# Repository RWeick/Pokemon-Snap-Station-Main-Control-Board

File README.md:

# Pokemon-Snap-Station-Main-Control-Board
The schematic and gerbers for an N64 Pokemon Snap Station Main Control Board

PCB Thickness: 1.6 mm

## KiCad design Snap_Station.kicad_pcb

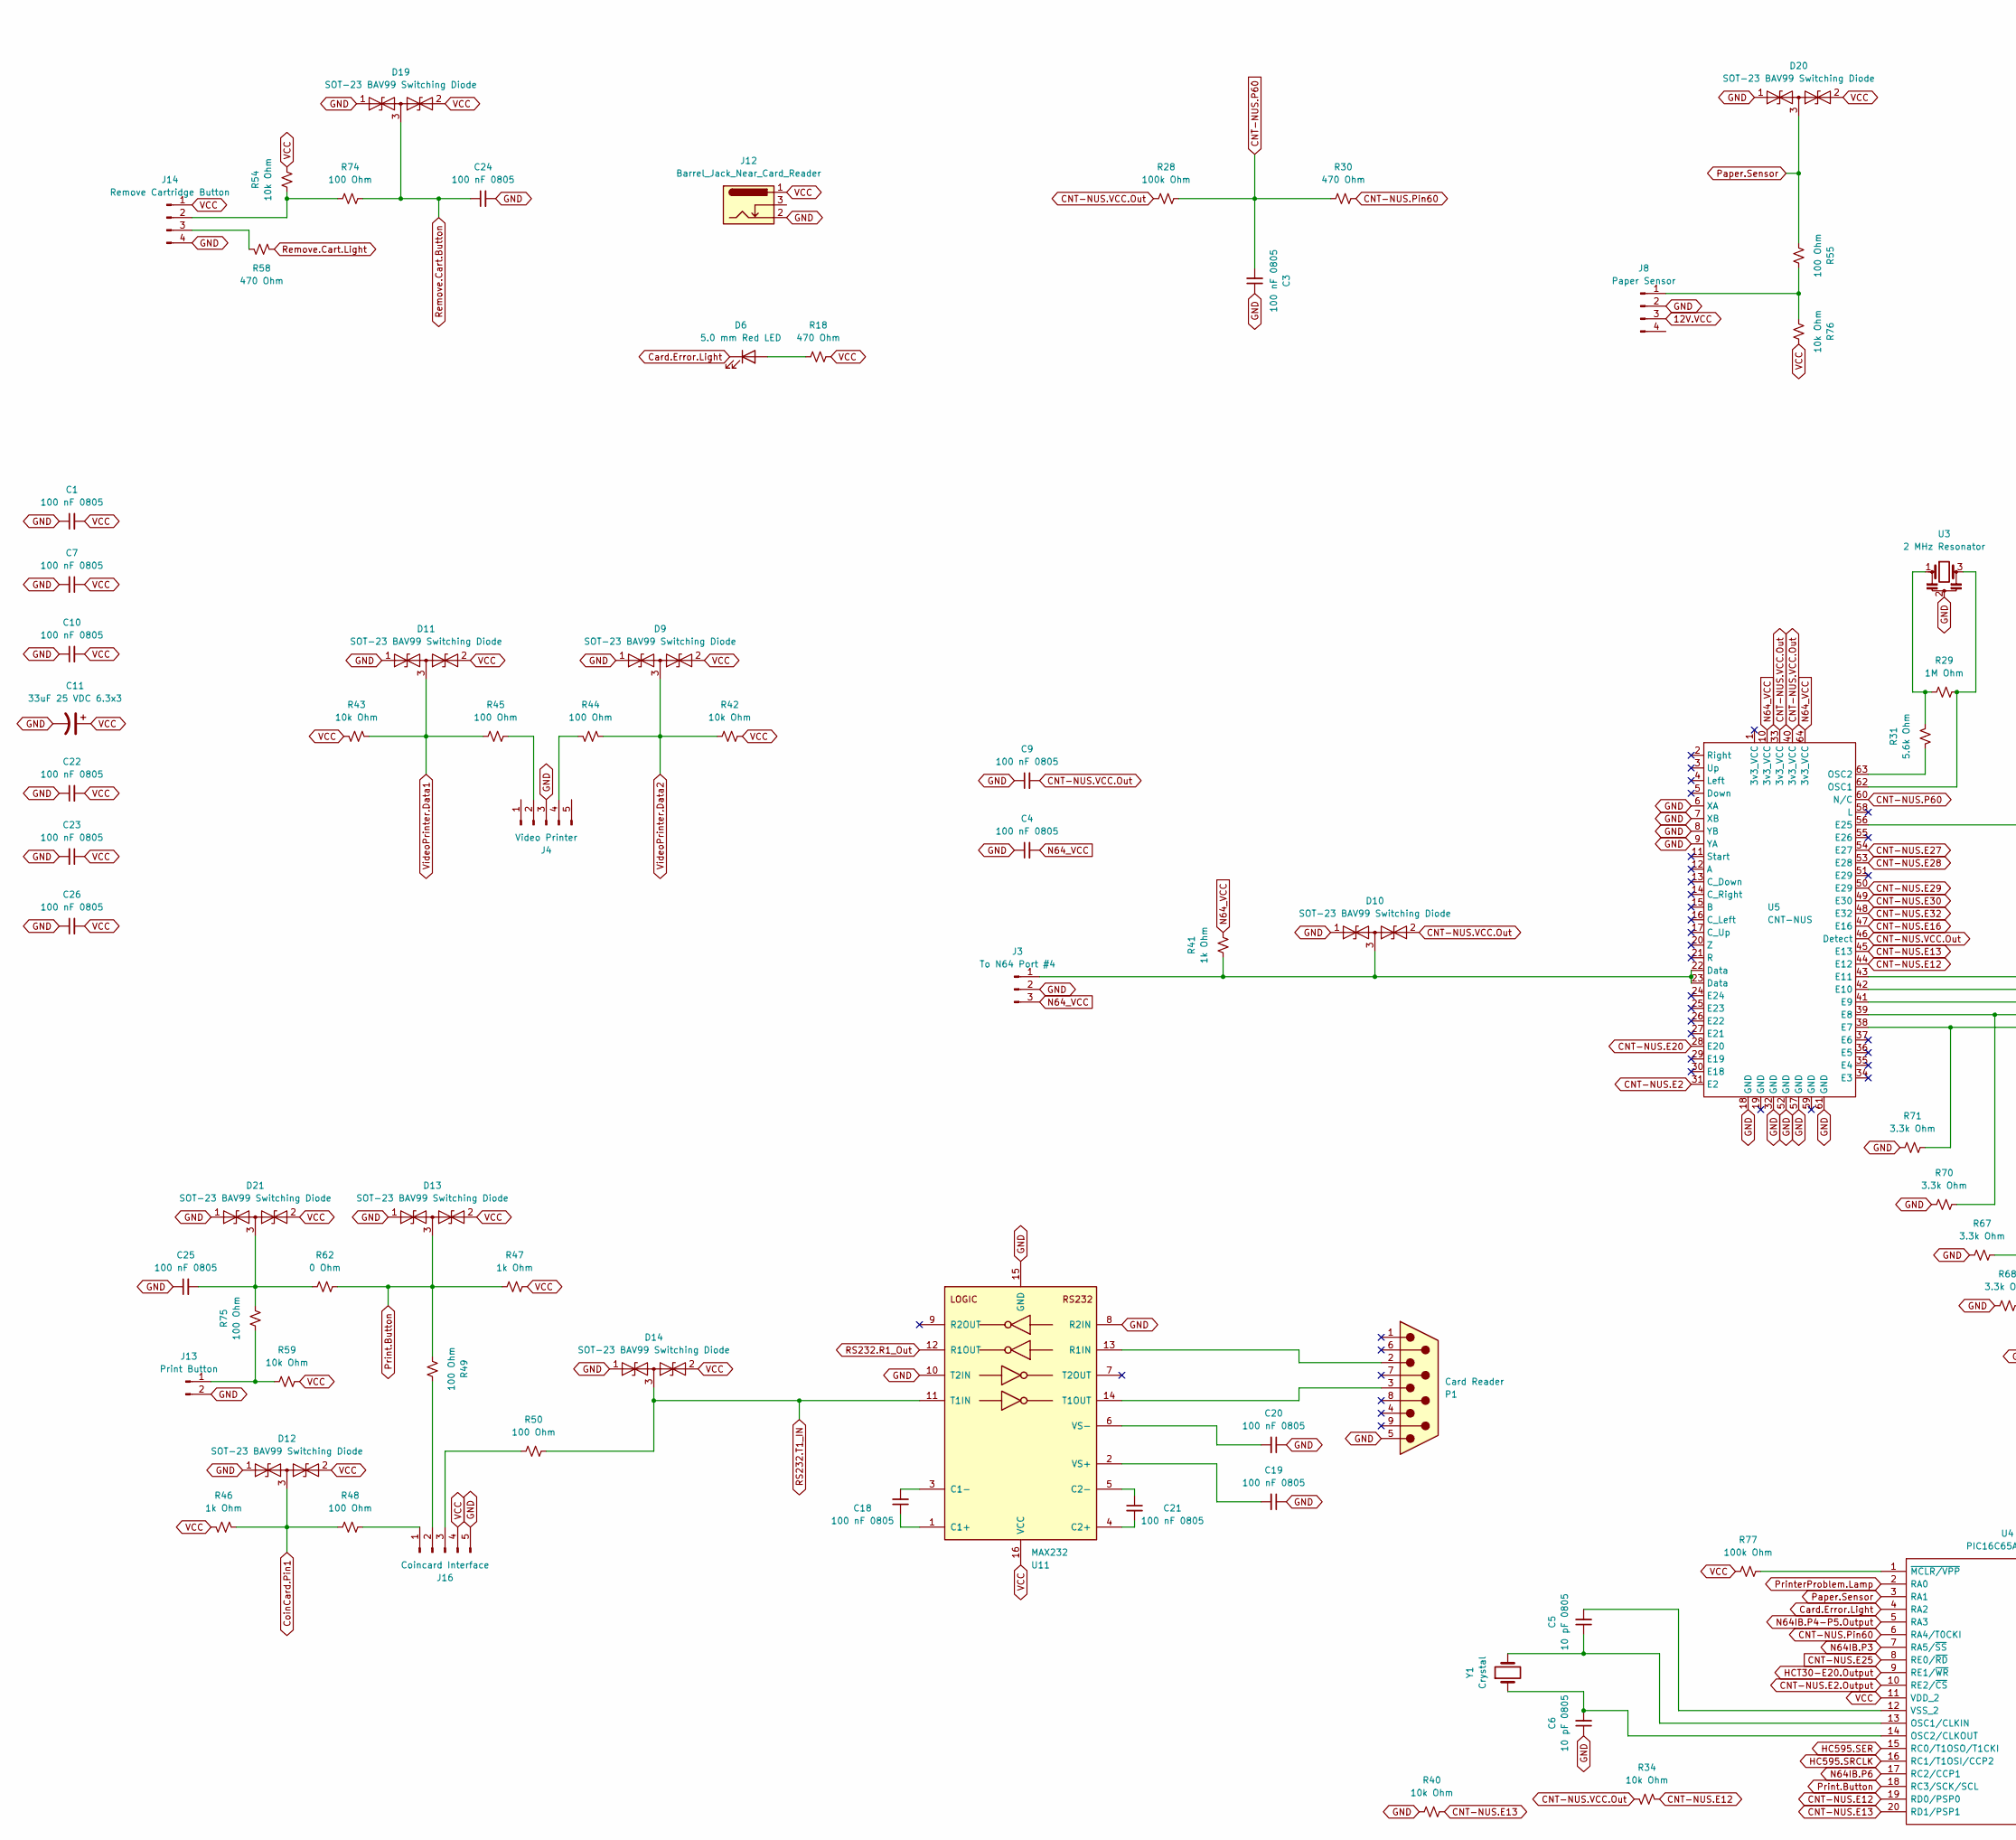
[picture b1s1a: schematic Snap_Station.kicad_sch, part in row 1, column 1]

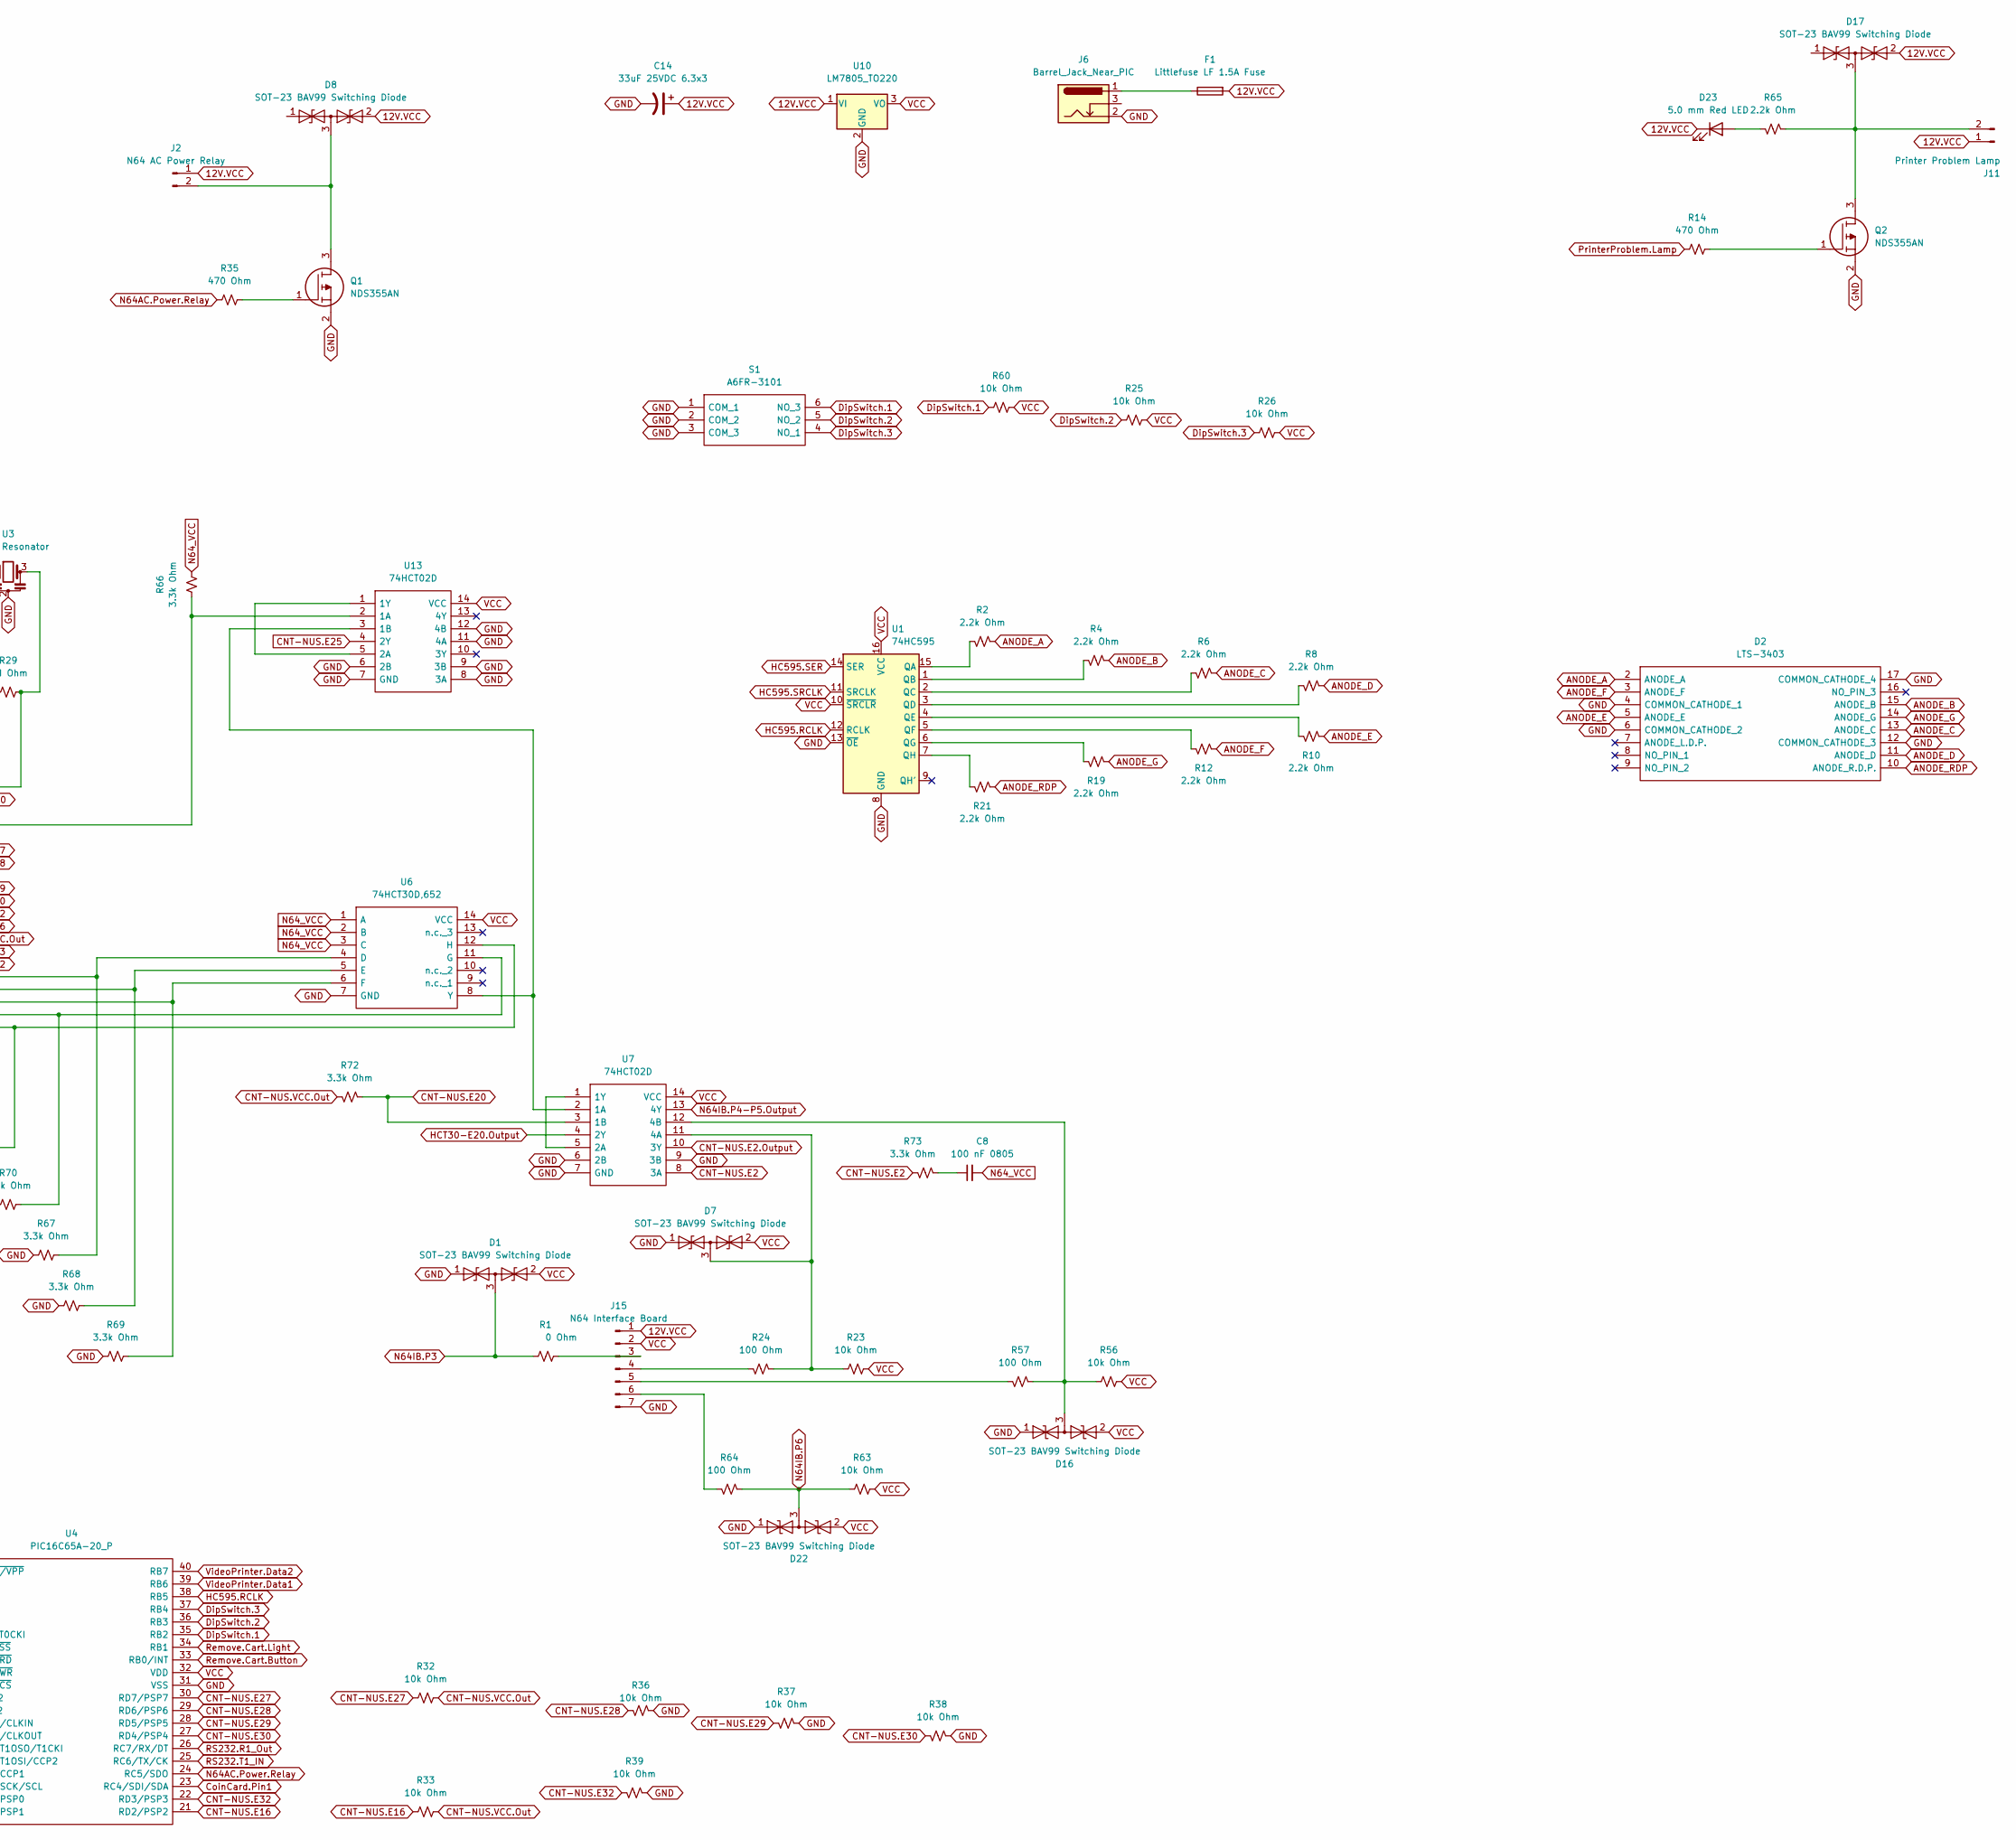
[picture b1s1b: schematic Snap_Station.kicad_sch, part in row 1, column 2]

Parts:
C1, C3, C4, C7, C8, C9, C10, C18, C19, C20, C21, C22, C23, C24, C25, C26: 100 nF 0805; C_0805_2012Metric_Pad1.18x1.45mm_HandSolder
C5, C6: 10 pF 0805; C_0805_2012Metric_Pad1.18x1.45mm_HandSolder
C11: 33uF 25 VDC 6.3x3; CP_Elec_6.3x3
C14: 33uF 25VDC 6.3x3; CP_Elec_6.3x3
D1, D7, D8, D9, D10, D11, D12, D13, D14, D16, D17, D19, D20, D21, D22: SOT-23 BAV99 Switching Diode; SOT-23
D2: LTS-3403; LTS3403LG; Manufacturer_Part_Number LTS-3403LG; Mouser Part Number 859-LTS-3403LG
D6, D23: 5.0 mm Red LED; LED_D5.0mm
F1: Littlefuse LF 1.5A Fuse; Littlefuse
J2: N64 AC Power Relay; PinHeader_1x02_P2.54mm_Vertical
J3: To N64 Port #4; Controller Cord
J4: Video Printer; Barrel Connector 5 Pin
J6: Barrel_Jack_Near_PIC; Barrel Jack
J8: Paper Sensor; PinHeader_1x04_P2.54mm_Vertical
J11: Printer Problem Lamp; PinHeader_1x02_P2.54mm_Vertical
J12: Barrel_Jack_Near_Card_Reader; Barrel Jack
J13: Print Button; PinHeader_1x02_P2.54mm_Vertical
J14: Remove Cartridge Button; PinHeader_1x04_P2.54mm_Vertical
J15: N64 Interface Board; PinHeader_1x07_P2.54mm_Vertical
J16: Coincard Interface; PinHeader_1x05_P2.54mm_Vertical
P1: Card Reader; DSUB-9_Male_Vertical_P2.77x2.84mm_MountingHoles
Q1, Q2: NDS355AN; Q's NDS356AP; Manufacturer_Part_Number NDS356AP; Mouser Part Number 512-NDS356AP
R1, R62: 0 Ohm; R_0805_2012Metric_Pad1.20x1.40mm_HandSolder
R2, R4, R6, R8, R10, R12, R19, R21, R65: 2.2k Ohm; R_0805_2012Metric_Pad1.20x1.40mm_HandSolder
R14, R18, R30, R35, R58: 470 Ohm; R_0805_2012Metric_Pad1.20x1.40mm_HandSolder
R23, R25, R26, R32, R33, R34, R36, R37, R38, R39, R40, R42, R43, R54, R56, R59, R60, R63, R76: 10k Ohm; R_0805_2012Metric_Pad1.20x1.40mm_HandSolder
R24, R44, R45, R48, R49, R50, R55, R57, R64, R74, R75: 100 Ohm; R_0805_2012Metric_Pad1.20x1.40mm_HandSolder
R28, R77: 100k Ohm; R_0805_2012Metric_Pad1.20x1.40mm_HandSolder
R29: 1M Ohm; R_0805_2012Metric_Pad1.20x1.40mm_HandSolder
R31: 5.6k Ohm; R_0805_2012Metric_Pad1.20x1.40mm_HandSolder
R41, R46, R47: 1k Ohm; R_0805_2012Metric_Pad1.20x1.40mm_HandSolder
R66, R67, R68, R69, R70, R71, R72, R73: 3.3k Ohm; R_0805_2012Metric_Pad1.20x1.40mm_HandSolder
S1: A6FR-3101; 3 Dip Switch; Manufacturer_Part_Number A6FR-3101; Mouser Part Number 653-A6FR-3101
U1: 74HC595; 74HC595D
U3: 2 MHz Resonator; 2mhz Resonator
U4: PIC16C65A-20_P; PIC16C65A; Manufacturer_Part_Number PIC16C65A-10/P
U5: CNT-NUS
U6: 74HCT30D,652; 74HC04M; Manufacturer_Part_Number 74HCT30D,652; Mouser Part Number 771-HCT30D652
U7, U13: 74HCT02D; 74HC04M; Manufacturer_Part_Number 74HCT02D; Mouser Part Number N/A
U10: LM7805_TO220; TO-220-3_Vertical
U11: MAX232
Y1: Crystal; Fox200

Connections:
12V.VCC: C14.1, D8.2 (A2), D17.2 (A2), D23.1 (K), F1.2, J2.1, J8.3, J11.1, J15.1, U10.1 (VI)
ANODE_A: D2.2 (ANODE_A), R2.1
ANODE_B: D2.15 (ANODE_B), R4.1
ANODE_C: D2.13 (ANODE_C), R6.1
ANODE_D: D2.11 (ANODE_D), R8.1
ANODE_E: D2.5 (ANODE_E), R10.1
ANODE_F: D2.3 (ANODE_F), R12.1
ANODE_G: D2.14 (ANODE_G), R19.1
ANODE_RDP: D2.10 (ANODE_R.D.P.), R21.1
CNT-NUS.E2: R73.1, U5.31 (E2), U7.8 (3A)
CNT-NUS.E2.Output: U4.10 (RE2/~CS), U7.10 (3Y)
CNT-NUS.E12: R34.1, U4.19 (RD0/PSP0), U5.44 (E12)
CNT-NUS.E13: R40.2, U4.20 (RD1/PSP1), U5.45 (E13)
CNT-NUS.E16: R33.1, U4.21 (RD2/PSP2), U5.47 (E16)
CNT-NUS.E20: R72.2, U5.28 (E20), U7.3 (1B)
CNT-NUS.E25: U4.8 (RE0/~RD), U13.4 (2Y)
CNT-NUS.E27: R32.1, U4.30 (RD7/PSP7), U5.54 (E27)
CNT-NUS.E28: R36.2, U4.29 (RD6/PSP6), U5.53 (E28)
CNT-NUS.E29: R37.2, U4.28 (RD5/PSP5), U5.50 (E29)
CNT-NUS.E30: R38.2, U4.27 (RD4/PSP4), U5.49 (E30)
CNT-NUS.E32: R39.2, U4.22 (RD3/PSP3), U5.48 (E32)
CNT-NUS.P60: C3.2, R28.2, R30.1, U5.60 (N/C)
CNT-NUS.Pin60: R30.2, U4.6 (RA4/T0CKI)
CNT-NUS.VCC.Out: C9.2, D10.2 (A2), R28.1, R32.2, R33.2, R34.2, R72.1, U5.33 (3v3_VCC), U5.40 (3v3_VCC), U5.46 (Detect)
Card.Error.Light: D6.1 (K), U4.4 (RA2)
CoinCard.Pin1: D12.3 (common), R46.1, R48.1, U4.23 (RC4/SDI/SDA)
DipSwitch.1: R60.1, S1.6 (NO_3), U4.35 (RB2)
DipSwitch.2: R25.1, S1.5 (NO_2), U4.36 (RB3)
DipSwitch.3: R26.1, S1.4 (NO_1), U4.37 (RB4)
GND: C1.1, C3.1, C4.1, C6.1, C7.2, C9.1, C10.1, C11.2, C14.2, C19.1, C20.1, C22.1, C23.2, C24.2, C25.1, C26.1, D1.1 (A1), D2.4 (COMMON_CATHODE_1), D2.6 (COMMON_CATHODE_2), D2.12 (COMMON_CATHODE_3), D2.17 (COMMON_CATHODE_4), D7.1 (A1), D9.1 (A1), D10.1 (A1), D11.1 (A1), D12.1 (A1), D13.1 (A1), D14.1 (A1), D16.1 (A1), D19.1 (A1), D20.1 (A1), D21.1 (A1), D22.1 (A1), J3.2, J4.3, J6.2, J8.2, J12.2, J13.2, J14.4, J15.7, J16.5, P1.5, Q1.2, Q2.2, R36.1, R37.1, R38.1, R39.1, R40.1, R67.2, R68.2, R69.2, R70.1, R71.1, S1.1 (COM_1), S1.2 (COM_2), S1.3 (COM_3), U1.8 (GND), U1.13 (~OE), U3.2, U4.31 (VSS), U5.6 (XA), U5.7 (XB), U5.8 (YB), U5.9 (YA), U5.18 (GND), U5.32 (GND), U5.52 (GND), U5.57 (GND), U5.61 (GND), U6.7 (GND), U7.6 (2B), U7.7 (GND), U7.9 (3B), U10.2 (GND), U11.8 (R2IN), U11.10 (T2IN), U11.15 (GND), U13.6 (2B), U13.7 (GND), U13.8 (3A), U13.9 (3B), U13.11 (4A), U13.12 (4B); also elsewhere on the board
HC595.RCLK: U1.12 (RCLK), U4.38 (RB5)
HC595.SER: U1.14 (SER), U4.15 (RC0/T1OSO/T1CKI)
HC595.SRCLK: U1.11 (SRCLK), U4.16 (RC1/T1OSI/CCP2)
HCT30-E20.Output: U4.9 (RE1/~WR), U7.4 (2Y)
N64AC.Power.Relay: R35.1, U4.24 (RC5/SDO)
N64IB.P3: D1.3 (common), R1.1, U4.7 (RA5/~SS)
N64IB.P4-P5.Output: U4.5 (RA3), U7.13 (4Y)
N64IB.P6: D22.3 (common), R63.2, R64.1, U4.17 (RC2/CCP1)
N64_VCC: C4.2, C8.2, J3.3, R41.1, R66.2, U5.10 (3v3_VCC), U5.64 (3v3_VCC), U6.1 (A), U6.2 (B), U6.3 (C)
unnamed: C8.1, R73.2
unnamed: D6.2 (A), R18.2
unnamed: D7.3 (common), R23.1, R24.1, U7.11 (4A)
unnamed: D8.3 (common), J2.2, Q1.3
unnamed: D10.3 (common), J3.1, R41.2, U5.22 (Data), U5.23 (Data)
unnamed: D16.3 (common), R56.2, R57.2, U7.12 (4B)
unnamed: D17.3 (common), J11.2, Q2.3, R65.2
unnamed: C25.2, D21.3 (common), R62.1, R75.2
unnamed: D23.2 (A), R65.1
unnamed: F1.1, J6.1
unnamed: J4.2, R45.2
unnamed: J4.4, R44.2
unnamed: J8.1, R55.1, R76.2
unnamed: J13.1, R59.1, R75.1
unnamed: J14.2, R54.1, R74.1
unnamed: J14.3, R58.2
unnamed: J15.3, R1.2
unnamed: J15.4, R24.2
unnamed: J15.5, R57.1
unnamed: J15.6, R64.2
unnamed: J16.1, R48.2
unnamed: J16.2, R49.2
unnamed: J16.3, R50.1
unnamed: Q1.1, R35.2
unnamed: Q2.1, R14.1
unnamed: R29.1, R31.1, U3.1
unnamed: R2.2, U1.15 (QA)
unnamed: R4.2, U1.1 (QB)
unnamed: R6.2, U1.2 (QC)
unnamed: R8.2, U1.3 (QD)
unnamed: R10.2, U1.4 (QE)
unnamed: R12.2, U1.5 (QF)
unnamed: R19.2, U1.6 (QG)
unnamed: R21.2, U1.7 (QH)
unnamed: C5.1, U4.13 (OSC1/CLKIN), Y1.2
unnamed: C6.2, U4.14 (OSC2/CLKOUT), Y1.1
unnamed: C5.2, U4.12 (VSS_2)
unnamed: R77.2, U4.1 (~MCLR/VPP)
unnamed: R71.2, U5.38 (E7), U6.12 (H)
unnamed: R70.2, U5.39 (E8), U6.11 (G)
unnamed: R69.1, U5.41 (E9), U6.6 (F)
unnamed: R68.1, U5.42 (E10), U6.5 (E)
unnamed: R67.1, U5.43 (E11), U6.4 (D)
unnamed: R29.2, U3.3, U5.62 (OSC1)
unnamed: R31.2, U5.63 (OSC2)
unnamed: U7.1 (1Y), U7.5 (2A)
unnamed: C18.1, U11.1 (C1+)
unnamed: C18.2, U11.3 (C1-)
unnamed: C21.2, U11.4 (C2+)
unnamed: C21.1, U11.5 (C2-)
unnamed: P1.2, U11.13 (R1IN)
unnamed: P1.3, U11.14 (T1OUT)
unnamed: C19.2, U11.2 (VS+)
unnamed: C20.2, U11.6 (VS-)
unnamed: R66.1, U5.56 (E25), U13.2 (1A)
unnamed: U6.8 (Y), U7.2 (1A), U13.3 (1B)
unnamed: U13.1 (1Y), U13.5 (2A)
Paper.Sensor: D20.3 (common), R55.2, U4.3 (RA1)
Print.Button: D13.3 (common), R47.1, R49.1, R62.2, U4.18 (RC3/SCK/SCL)
PrinterProblem.Lamp: R14.2, U4.2 (RA0)
RS232.R1_Out: U4.26 (RC7/RX/DT), U11.12 (R1OUT)
RS232.T1_IN: D14.3 (common), R50.2, U4.25 (RC6/TX/CK), U11.11 (T1IN)
Remove.Cart.Button: C24.1, D19.3 (common), R74.2, U4.33 (RB0/INT)
Remove.Cart.Light: R58.1, U4.34 (RB1)
VCC: C1.2, C7.1, C10.2, C11.1, C22.2, C23.1, C26.2, D1.2 (A2), D7.2 (A2), D9.2 (A2), D11.2 (A2), D12.2 (A2), D13.2 (A2), D14.2 (A2), D16.2 (A2), D19.2 (A2), D20.2 (A2), D21.2 (A2), D22.2 (A2), J12.1, J14.1, J15.2, J16.4, R18.1, R23.2, R25.2, R26.2, R42.2, R43.2, R46.2, R47.2, R54.2, R56.1, R59.2, R60.2, R63.1, R76.1, R77.1, U1.10 (~SRCLR), U1.16 (VCC), U4.11 (VDD_2), U4.32 (VDD), U6.14 (VCC), U7.14 (VCC), U10.3 (VO), U11.16 (VCC), U13.14 (VCC)
VideoPrinter.Data1: D11.3 (common), R43.1, R45.1, U4.39 (RB6)
VideoPrinter.Data2: D9.3 (common), R42.1, R44.1, U4.40 (RB7)

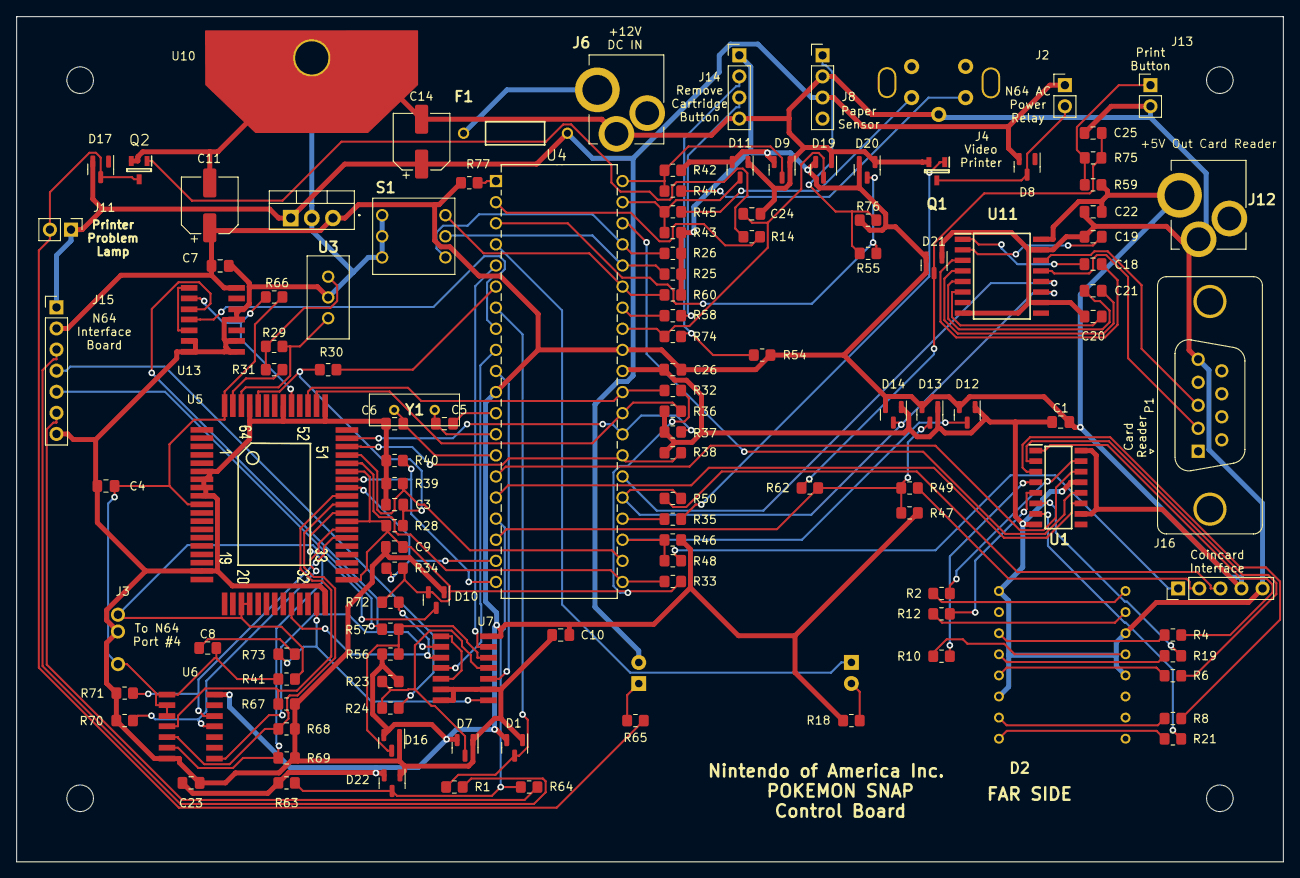
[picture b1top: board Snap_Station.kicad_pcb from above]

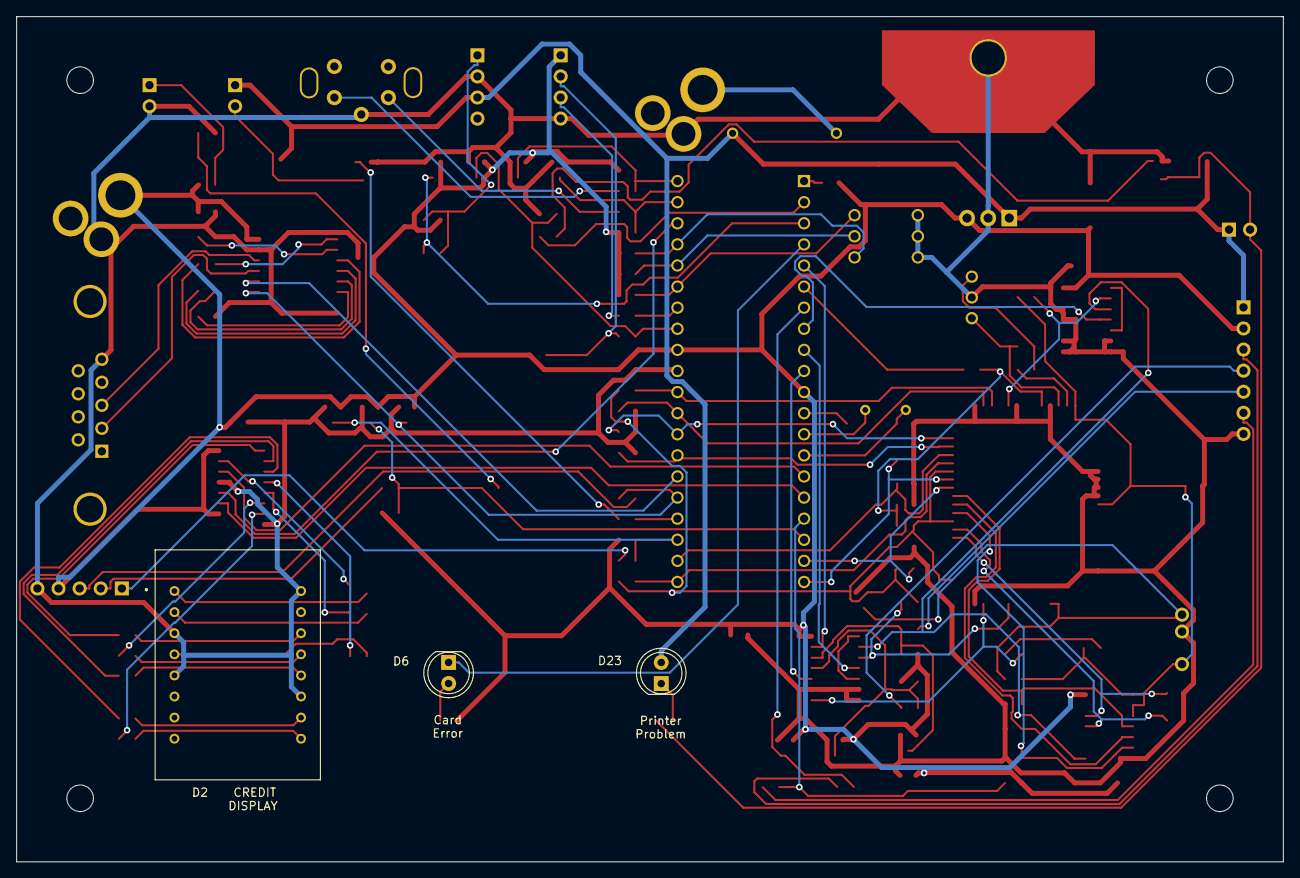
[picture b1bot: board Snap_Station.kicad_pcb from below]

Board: 2 copper layers, 152.5 x 101.7 mm, 130 parts (3 on the bottom side), 106 nets.

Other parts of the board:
7805Gnd: 7805 Heatsink
Hole1, Hole2, Hole3, Hole4: MountingHole_3.2mm_M3

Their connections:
GND: 7805Gnd.1; also elsewhere on the board
